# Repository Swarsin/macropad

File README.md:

# macropad

It's a 3x3 macropad pcb, which I designed in KiCad. The microcontroller I used is a Raspberry Pi Pico, which I had several of laying around. Other parts include an oled display, rotary encoder switch (EC11), and mx-style switches, all of which need to be soldered on.

I also wrote some bare-metal C++ firmware for it and modelled an angled 3d-printed case in FreeCAD. The firmware is in `firmware/`, the case files are in `cad/`, and the old CircuitPython/KMK test script is still in `firmware.py`.

Images (3D):

## pins

The 3x3 matrix uses GP0-GP2 for rows and GP3-GP5 for columns. The diodes are COL2ROW, with the anode on the switch/column side and the cathode on the row net:

- rows: `GP0` (pin 1), `GP1` (pin 2), `GP2` (pin 4), inputs with pull-downs
- columns: `GP3` (pin 5), `GP4` (pin 6), `GP5` (pin 7), driven high one at a time
- encoder: `A` on `GP17` (pin 22), `B` on `GP16` (pin 21), push switch on `GP18` (pin 24)
- oled: `SDA` on `GP8` (pin 11), `SCL` on `GP9` (pin 12), address `0x3C`

The encoder and OLED both use internal pull-ups, so the encoder common pins can go straight to GND.

I ran ERC and DRC in KiCad 10; both report 0 errors. The remaining warnings are mostly missing external library paths and silkscreen clipping.

## firmware

The firmware is a superloop built with the Pico C/C++ SDK and TinyUSB. It does not use an RTOS.

- the matrix is scanned once per millisecond. One column is driven high, the code waits 5 us for the diodes and traces to settle, then the row inputs are read.
- every key has its own 5 ms debounce timer. Raw state, debounced state and press/release edges are kept separately, so the main loop never blocks on a key.
- the encoder is decoded with a 16-entry Gray-code table. The push switch has a 10 ms debounce.
- USB is a single HID interface with two report IDs: a 6-key rollover keyboard report and a consumer control report. The encoder sends volume up/down and the push switch sends mute.
- the OLED is optional. If it does not ACK on the I2C bus the firmware keeps running without it.

Build it with the Pico SDK and an ARM toolchain:

```bash
cd firmware
mkdir build
cd build
cmake .. -DPICO_SDK_PATH=/path/to/pico-sdk
cmake --build . -j
```

If `PICO_SDK_PATH` is not set, you can use `-DPICO_SDK_FETCH_FROM_GIT=ON` instead. The build produces `macropad_firmware.uf2`, `.elf` and `.bin` files. The GitHub Actions workflow builds the same target and uploads the UF2 as a workflow artifact. Hold BOOTSEL while plugging the Pico in, then copy the UF2 to the `RPI-RP2` drive.

The keymap is in `firmware/include/config.h`. S1-S9 are mapped to 1-9 by default. Change `KEYMAP` there if you want different HID keycodes.

## enclosure

The case is a two-part print for the 95.25 x 95.885 mm board. It has a 6.5 degree typing angle, a 1.5 mm shelf around the PCB, and a deeper area under the board for the through-hole diodes. The top cover has 14 x 14 mm switch cutouts, a 12.5 mm hole for the encoder and a 28 x 15 mm OLED window. It is held on with four snap-fit hooks in the side walls.

The STL files are in `cad/`. Print the bottom flat on its base and the top upside down on its top face. I used PLA at 0.2 mm layers, 3 walls and 20% infill; PETG should also work. No supports are needed.

Assembly is just dropping the populated PCB into the bottom case, lining the Pico USB connector up with the rear opening, and pressing the top cover on until the hooks click. The switches should line up with the plate cutouts as the top goes down.

The FreeCAD project and STEP export are in `cad/`. To regenerate them, run:

```bash
freecadcmd cad/export_enclosure.py
```

That re-exports `cad/Macropad_Enclosure.step` and both STL files from the included `cad/Macropad_Enclosure.FCStd`.

This project includes the Arch Linux logo, which is a trademark of the Arch Linux Project. The use of this logo does not imply any endorsement or affiliation with Arch Linux. For more details, see the Arch Linux Trademark Policy.

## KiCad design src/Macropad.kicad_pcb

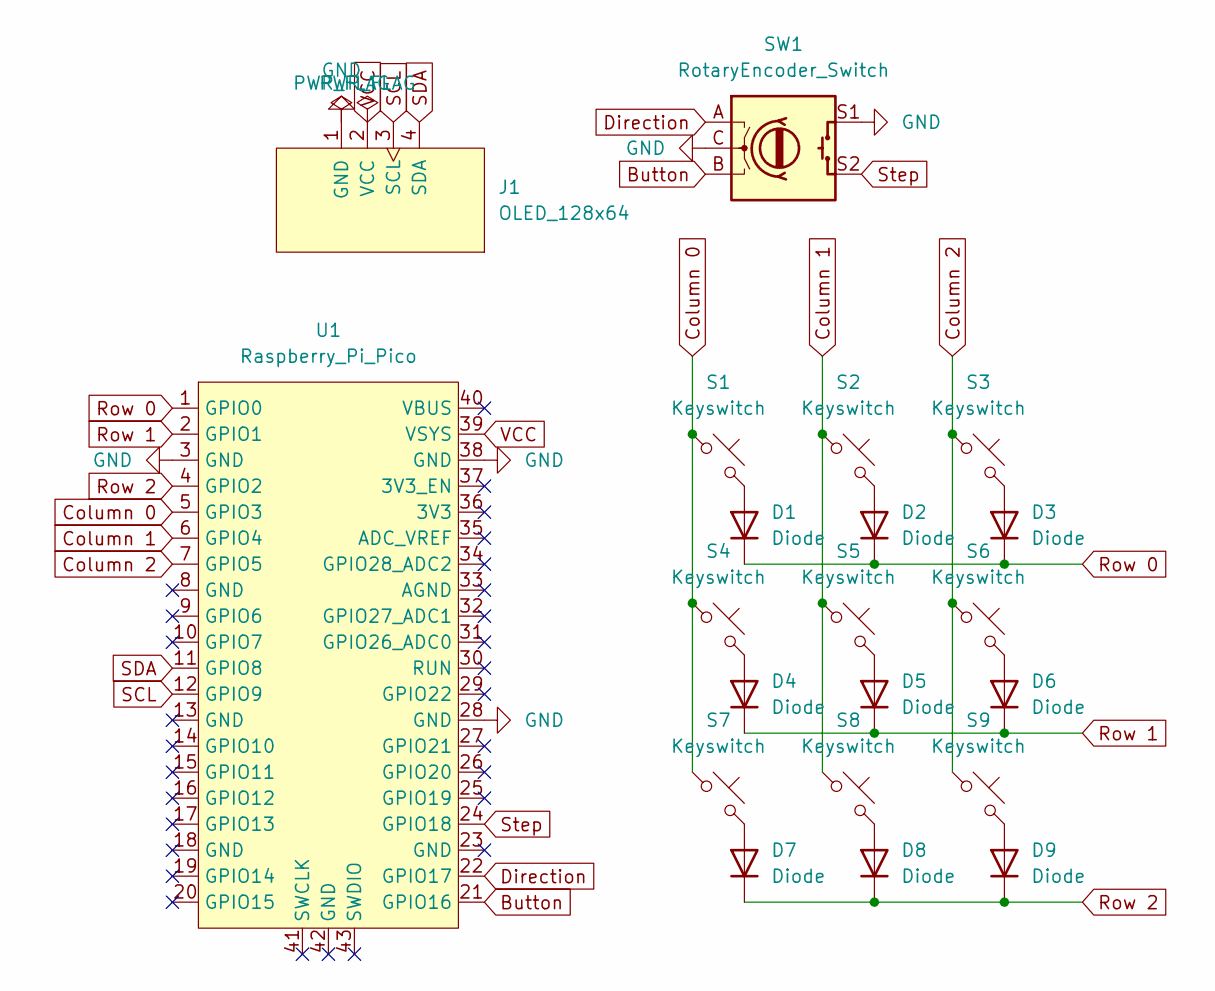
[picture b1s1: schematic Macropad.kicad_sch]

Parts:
D1, D2, D3, D4, D5, D6, D7, D8, D9: Diode; Diode_DO-35
J1: OLED_128x64
S1, S2, S3, S4, S5, S6, S7, S8, S9: Keyswitch; MX_PCB_1.00u
SW1: RotaryEncoder_Switch; RotaryEncoder_Alps_EC11E-Switch_Vertical_H20mm
U1: Raspberry_Pi_Pico

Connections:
Button: SW1.B, U1.21 (GPIO16)
Column 0: S1.1, S4.1, S7.1, U1.5 (GPIO3)
Column 1: S2.1, S5.1, S8.1, U1.6 (GPIO4)
Column 2: S3.1, S6.1, S9.1, U1.7 (GPIO5)
Direction: SW1.A, U1.22 (GPIO17)
GND: J1.1 (GND), SW1.C, SW1.S1, U1.3 (GND), U1.28 (GND), U1.38 (GND)
unnamed: D1.2 (A), S1.2
unnamed: D2.2 (A), S2.2
unnamed: D3.2 (A), S3.2
unnamed: D4.2 (A), S4.2
unnamed: D5.2 (A), S5.2
unnamed: D6.2 (A), S6.2
unnamed: D7.2 (A), S7.2
unnamed: D8.2 (A), S8.2
unnamed: D9.2 (A), S9.2
Row 0: D1.1 (K), D2.1 (K), D3.1 (K), U1.1 (GPIO0)
Row 1: D4.1 (K), D5.1 (K), D6.1 (K), U1.2 (GPIO1)
Row 2: D7.1 (K), D8.1 (K), D9.1 (K), U1.4 (GPIO2)
SCL: J1.3 (SCL), U1.12 (GPIO9)
SDA: J1.4 (SDA), U1.11 (GPIO8)
Step: SW1.S2, U1.24 (GPIO18)
VCC: J1.2 (VCC), U1.39 (VSYS)

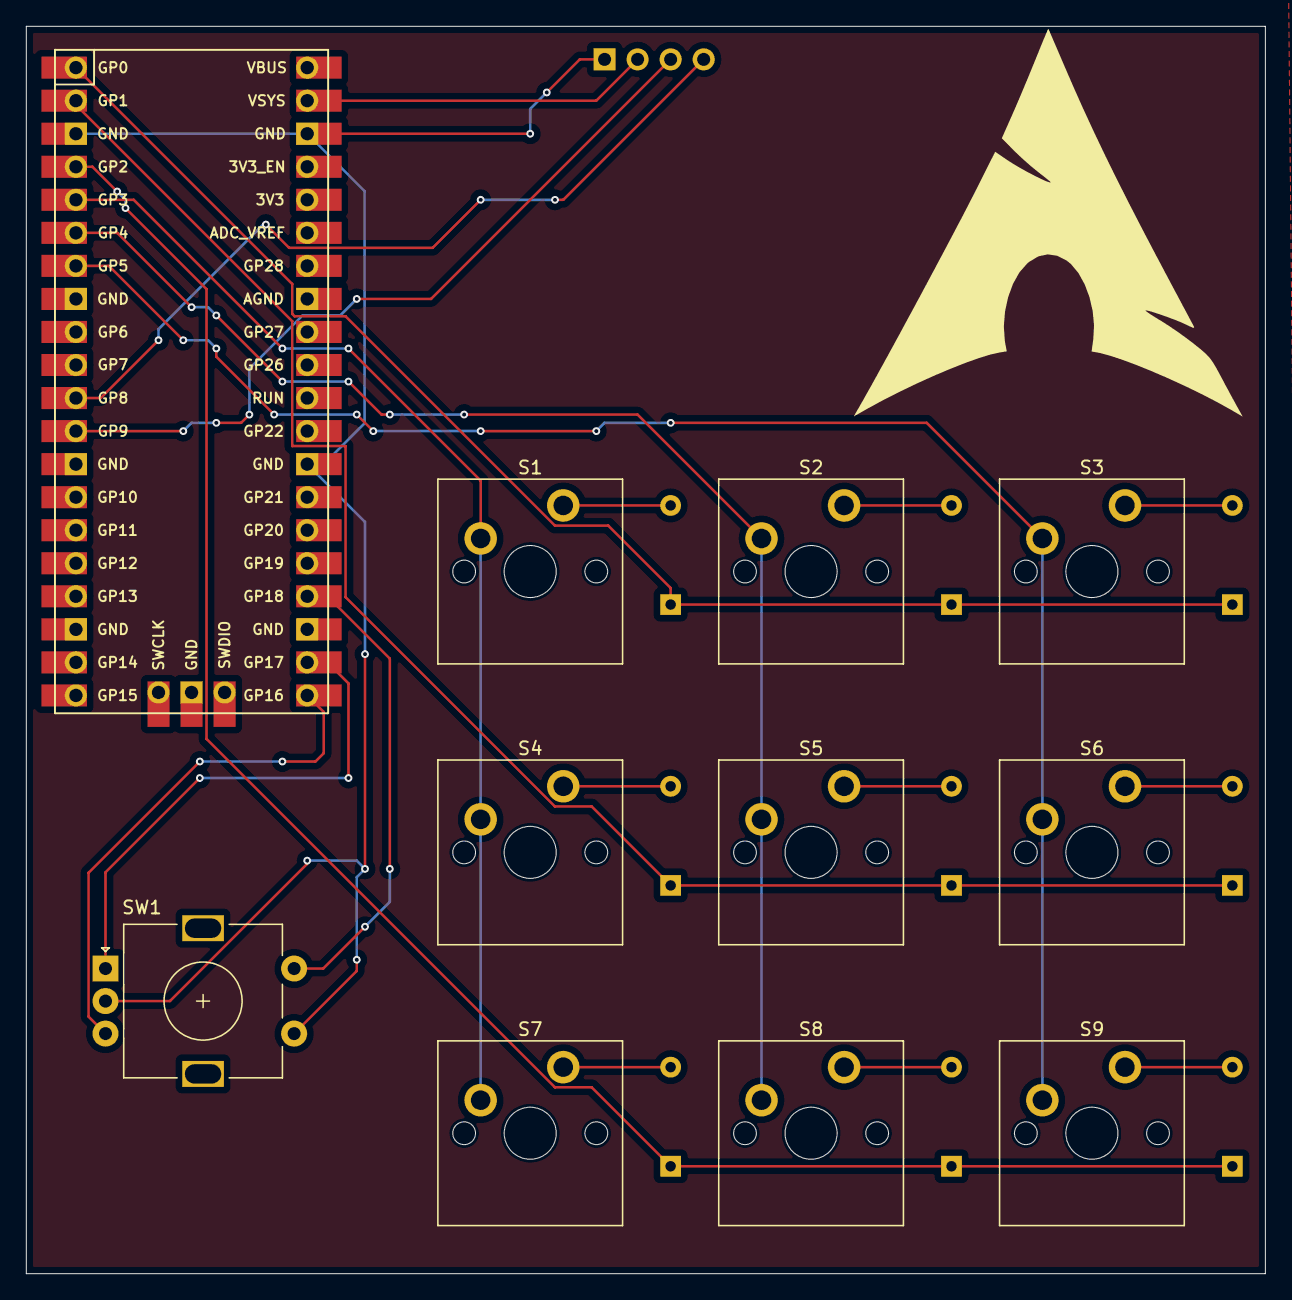
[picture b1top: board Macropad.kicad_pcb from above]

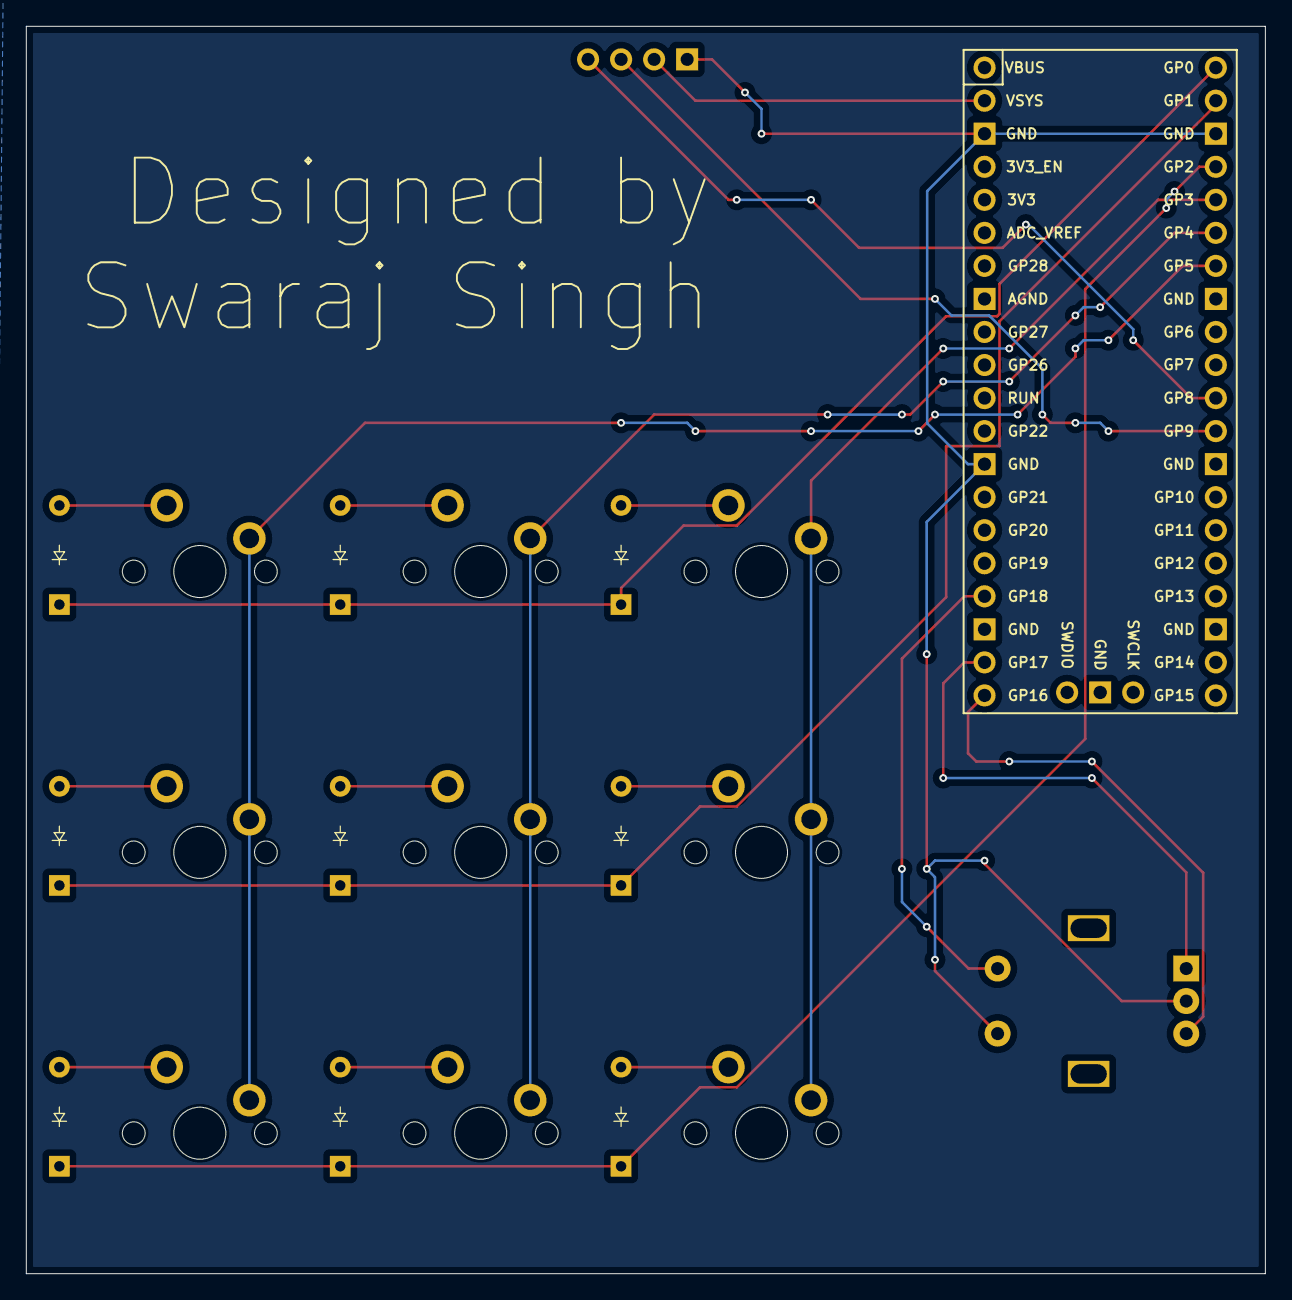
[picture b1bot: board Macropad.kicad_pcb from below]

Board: 2 copper layers, 95.2 x 95.9 mm, 21 parts (9 on the bottom side), 22 nets.

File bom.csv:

Designator,Footprint,Quantity,Value,Manufacturer,MPN,Supplier,Notes
"D1, D2, D3, D4, D5, D6, D7, D8, D9",Diode_DO-35,9,1N4148,onsemi,1N4148,Digi-Key,Through-hole; cathode stripe to row net
J1,OLED_128x64,1,0.96in SSD1306 I2C OLED,Generic,TBD,TBD,4-pin 0.1in header; 3.3V or 5V module
"S1, S2, S3, S4, S5, S6, S7, S8, S9",MX_PCB_1.00u,9,Cherry MX Red,Cherry,MX1A-11NW,Digi-Key,PCB-mount 1u; keycaps not included
SW1,RotaryEncoder_Alps_EC11E-Switch_Vertical_H20mm,1,EC11E rotary encoder with push,Alps,EC11E15244B2,Digi-Key,20 mm shaft; common pins to GND
U1,Raspberry_Pi_Pico,1,Raspberry Pi Pico,Raspberry Pi,SC0915,Digi-Key,RP2040 module; headers not included

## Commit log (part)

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2025-01-23 Create d
